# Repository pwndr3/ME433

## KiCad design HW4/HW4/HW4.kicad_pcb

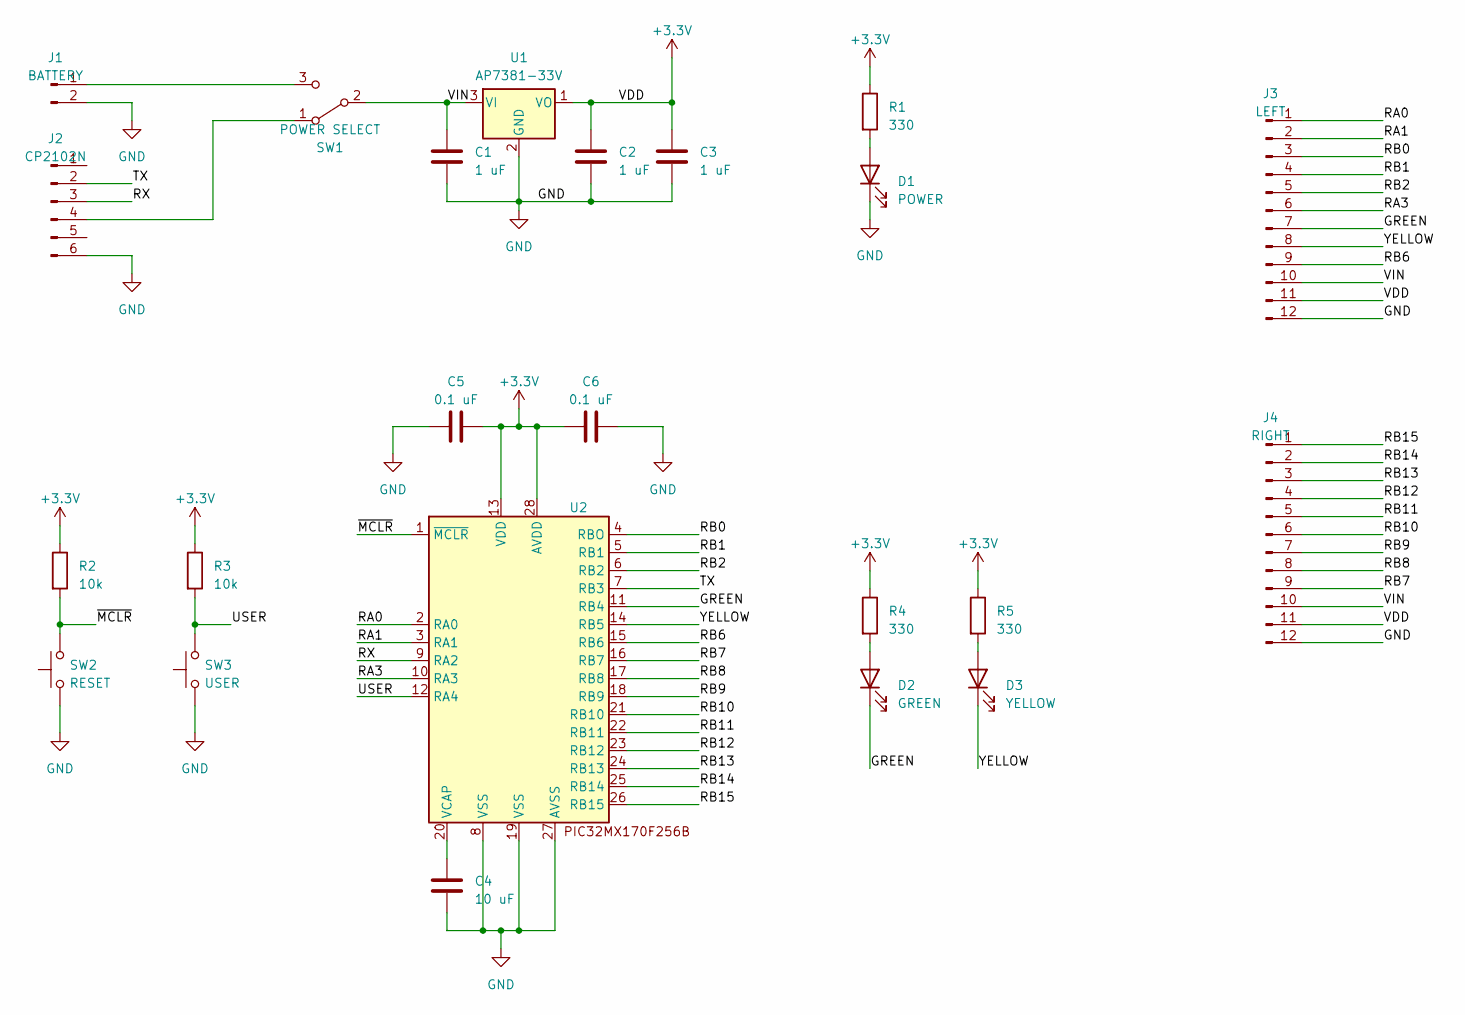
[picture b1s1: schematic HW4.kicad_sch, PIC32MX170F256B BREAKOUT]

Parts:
C1, C2, C3: 1 uF; C_Disc_D3.4mm_W2.1mm_P2.50mm
C4: 10 uF; C_Disc_D3.8mm_W2.6mm_P2.50mm
C5, C6: 0.1 uF; C_Disc_D3.8mm_W2.6mm_P2.50mm
D1: POWER; LED_D3.0mm
D2: GREEN; LED_D3.0mm
D3: YELLOW; LED_D3.0mm
J1: BATTERY; PinHeader_1x02_P2.54mm_Vertical
J2: CP2102N; PinHeader_1x06_P2.54mm_Vertical
J3: LEFT; PinHeader_1x12_P2.54mm_Vertical
J4: RIGHT; PinHeader_1x12_P2.54mm_Vertical
R1, R4, R5: 330; R_Axial_DIN0207_L6.3mm_D2.5mm_P7.62mm_Horizontal
R2, R3: 10k; R_Axial_DIN0207_L6.3mm_D2.5mm_P7.62mm_Horizontal
SW1: POWER SELECT; SWITCH
SW2: RESET; PUSH
SW3: USER; PUSH
U1: AP7381-33V; TO-92_Inline_Wide
U2: DIP-28_W7.62mm_Socket

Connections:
+3.3V: C2.1, C3.1, C5.2, C6.1, J3.11, J4.11, R1.1, R2.1, R3.1, R4.1, R5.1, U1.1 (VO), U2.13 (VDD), U2.28 (AVDD)
/GREEN: D2.1 (K), J3.7, U2.11 (RB4)
/RA0: J3.1, U2.2 (RA0)
/RA1: J3.2, U2.3 (RA1)
/RA3: J3.6, U2.10 (RA3)
/RB0: J3.3, U2.4 (RBO)
/RB1: J3.4, U2.5 (RB1)
/RB2: J3.5, U2.6 (RB2)
/RB6: J3.9, U2.15 (RB6)
/RB7: J4.9, U2.16 (RB7)
/RB8: J4.8, U2.17 (RB8)
/RB9: J4.7, U2.18 (RB9)
/RB10: J4.6, U2.21 (RB10)
/RB11: J4.5, U2.22 (RB11)
/RB12: J4.4, U2.23 (RB12)
/RB13: J4.3, U2.24 (RB13)
/RB14: J4.2, U2.25 (RB14)
/RB15: J4.1, U2.26 (RB15)
/RX: J2.3, U2.9 (RA2)
/TX: J2.2, U2.7 (RB3)
/USER: R3.2, SW3.2, U2.12 (RA4)
/VIN: C1.1, J3.10, J4.10, SW1.2 (B), U1.3 (VI)
/YELLOW: D3.1 (K), J3.8, U2.14 (RB5)
/~MCLR: R2.2, SW2.2, U2.1 (~MCLR)
GND: C1.2, C2.2, C3.2, C4.1, C5.1, C6.2, D1.1 (K), J1.2, J2.6, J3.12, J4.12, SW2.1, SW3.1, U1.2 (GND), U2.8 (VSS), U2.19 (VSS), U2.27 (AVSS)
unnamed: D1.2 (A), R1.2
unnamed: D2.2 (A), R4.2
unnamed: D3.2 (A), R5.2
unnamed: J1.1, SW1.3 (C)
unnamed: J2.4, SW1.1 (A)
unnamed: C4.2, U2.20 (VCAP)

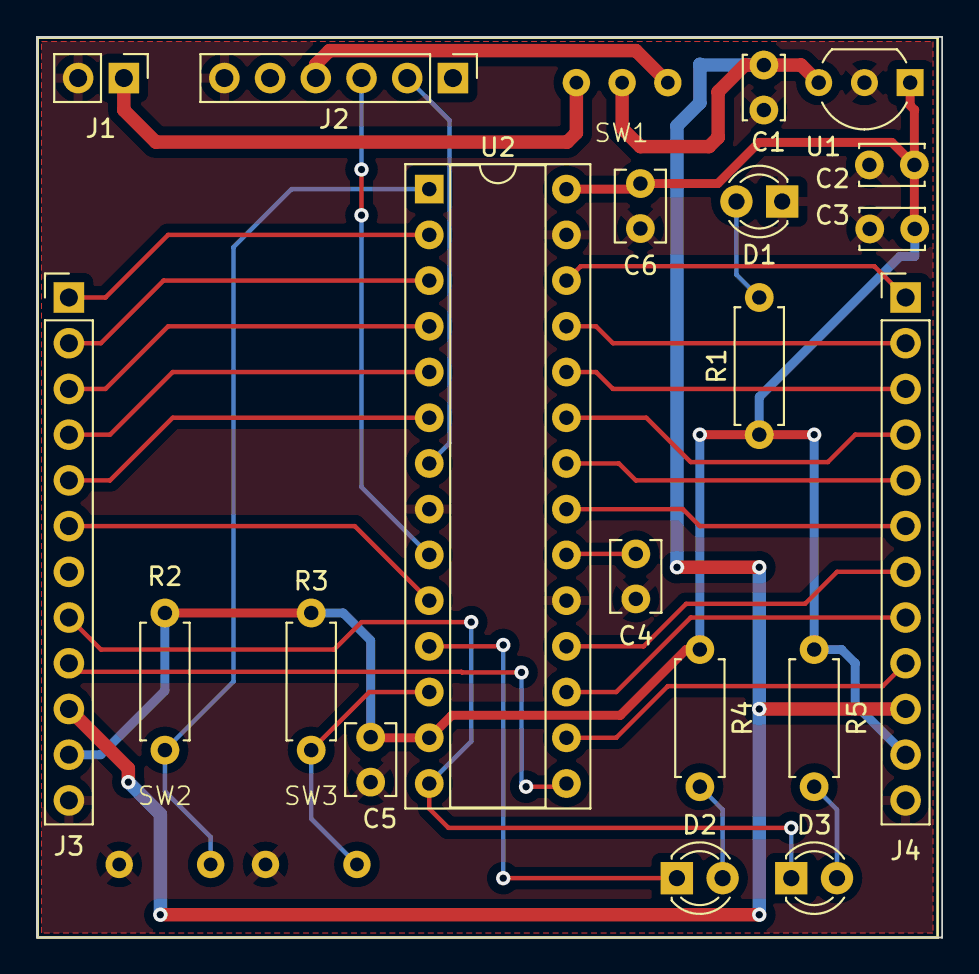
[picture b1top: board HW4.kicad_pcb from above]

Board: 2 copper layers, 50.3 x 50.0 mm, 23 parts (0 on the bottom side), 31 nets.

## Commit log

2023-03-31 Added template files for HW2
2023-04-01 Fixed bootloader and HW2 done
2023-04-01 Added circuit schematic
2023-04-04 HW3 done
2023-04-07 PIC32 breakout board schematic
2023-04-16 HW4 in the making; HW5 practically done, need to test on the scope
2023-04-18 Final code for HW5
2023-04-18 Added pictures
2023-04-19 HW6 working
2023-04-22 HW7 completed
2023-04-22 HW8 completed
2023-04-22 Added some comments and minor fixes for HW8
2023-04-27 Finished HW9
2023-05-03 HW10 completed
2023-05-10 HW11 completed
2023-05-19 HW13 done
2023-05-25 HW14 completed
2023-06-02 Working on HW15 and HW16
2023-06-02 PICO <-> PIC UART connection working
2023-06-03 HW4 done
2023-06-04 HW12 completed
2023-06-07 New bot design version
2023-06-07 Far from perfect line detection; good enough for HW15
2023-06-07 POC line detection
2023-06-07 Code in the making for line detection
2023-06-07 Line detection basically completed
2023-06-07 Better HW15 - based on work for TechCup
2023-06-08 Could not get a line detection working for the colored map, so leaving last bit of work here
